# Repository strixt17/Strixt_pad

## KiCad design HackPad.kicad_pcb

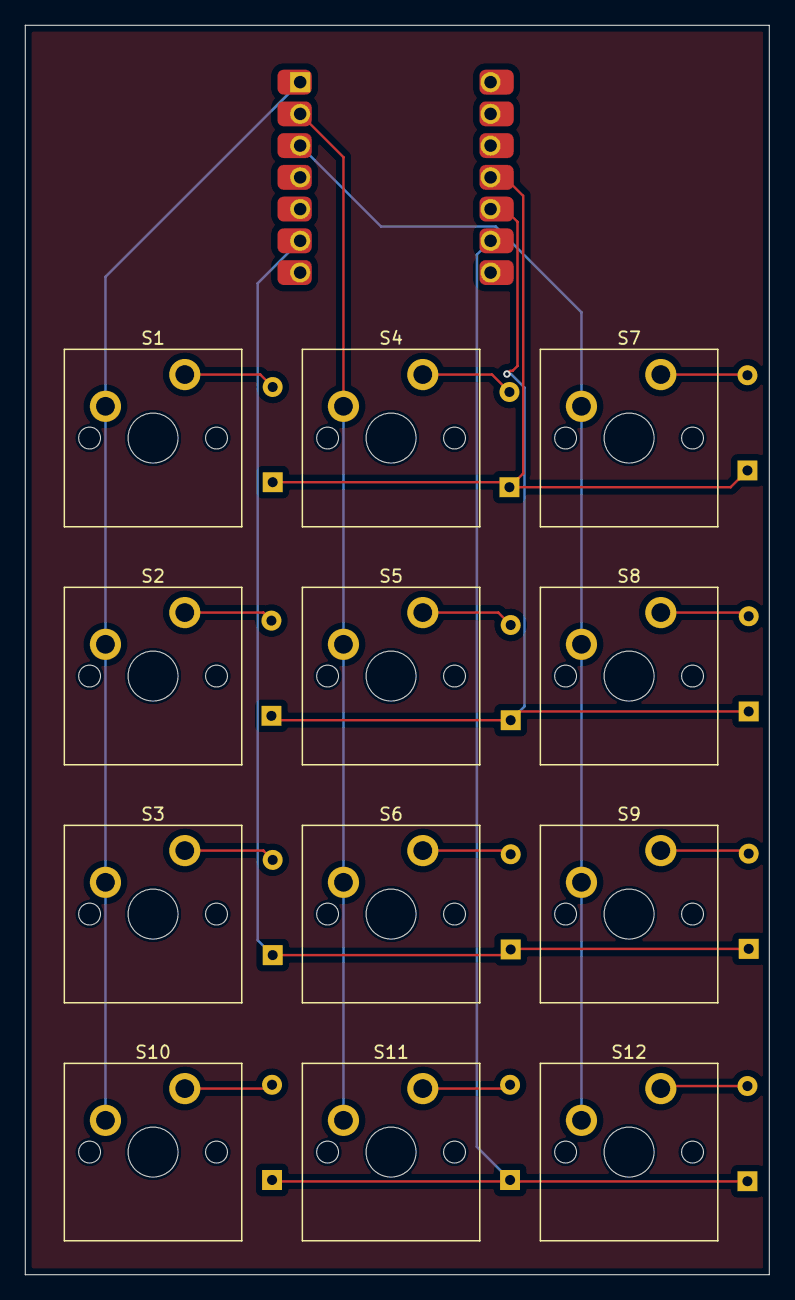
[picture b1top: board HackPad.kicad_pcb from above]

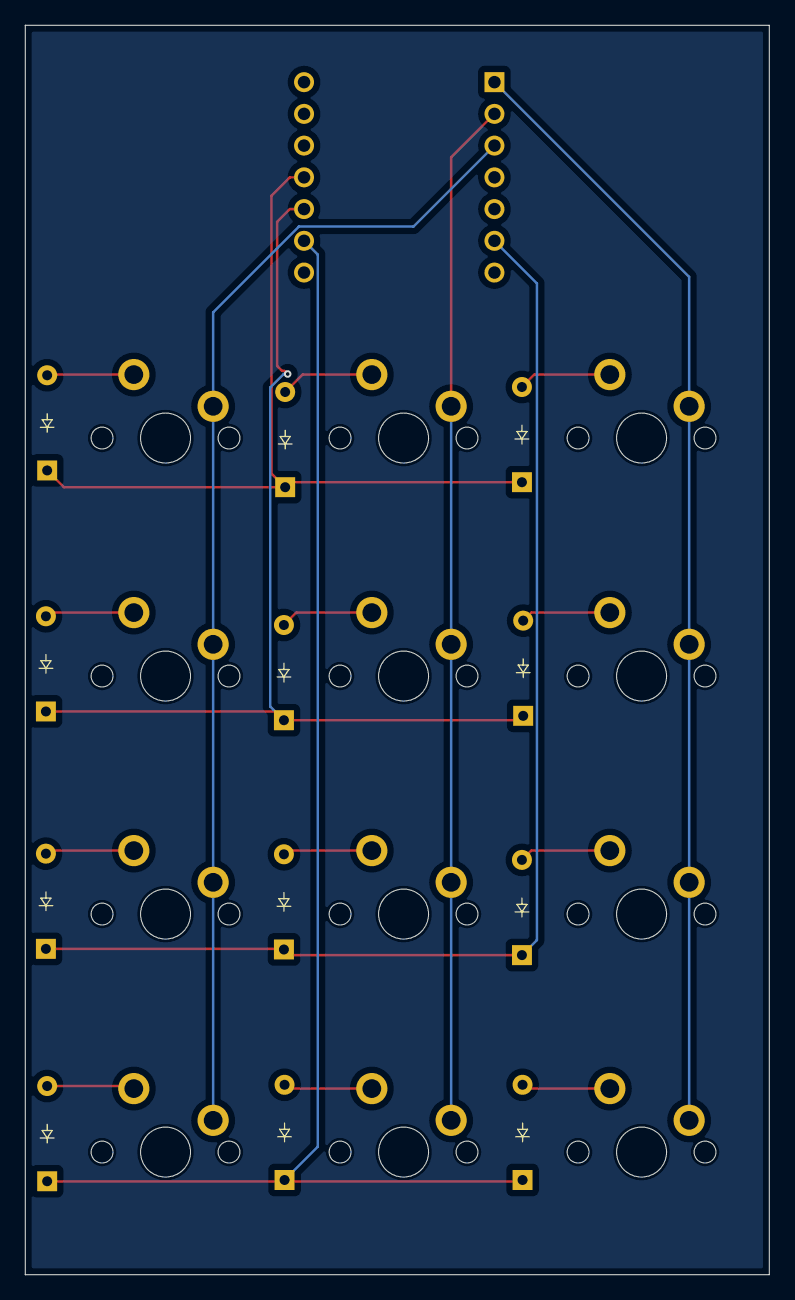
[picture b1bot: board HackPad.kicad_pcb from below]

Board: 2 copper layers, 59.5 x 100.0 mm, 25 parts (12 on the bottom side), 19 nets.

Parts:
D1, D2, D3, D4, D5, D6, D7, D8, D9, D10, D11, D12: Diode; Diode_DO-35
S1, S2, S3, S4, S5, S6, S7, S8, S9, S10, S11, S12: Keyswitch; MX_PCB_1.00u
U1: MCU_Seeed_XIAO_RP2040; Seeed_XIAO_RP2040

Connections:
Column 0: S1.1, S2.1, S3.1, S10.1, U1.1 (PA02_A0_D0)
Column 1: S4.1, S5.1, S6.1, S11.1, U1.2 (PA4_A1_D1)
Column 2: S7.1, S8.1, S9.1, S12.1, U1.3 (PA10_A2_D2)
unnamed: D1.2 (A), S1.2
unnamed: D2.2 (A), S2.2
unnamed: D3.2 (A), S3.2
unnamed: D4.2 (A), S4.2
unnamed: D5.2 (A), S5.2
unnamed: D6.2 (A), S6.2
unnamed: D7.2 (A), S7.2
unnamed: D8.2 (A), S8.2
unnamed: D9.2 (A), S9.2
unnamed: D10.2 (A), S10.2
unnamed: D11.2 (A), S11.2
unnamed: D12.2 (A), S12.2
Row 0: D1.1 (K), D4.1 (K), D7.1 (K), U1.11 (PA6_A10_D10_MOSI)
Row 1: D2.1 (K), D5.1 (K), D8.1 (K), U1.10 (PA5_A9_D9_MISO)
Row 2: D3.1 (K), D6.1 (K), D9.1 (K), U1.6 (PA9_A5_D5_SCL)
Row 3: D10.1 (K), D11.1 (K), D12.1 (K), U1.9 (PA7_A8_D8_SCK)

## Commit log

2024-10-21 Create pcb
2024-10-22 Create cad
2024-10-22 adding stl file
    adding stl file
2024-10-22 Create firmware
